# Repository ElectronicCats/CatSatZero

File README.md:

# CaTSatZero

Kit CatSat Zero Education

Manual and more information in our [Wiki](https://github.com/ElectronicCats/CatSatZero/wiki)

Electronic Cats invests time and resources providing this open source design, please support Electronic Cats and open-source hardware by purchasing products from Electronic Cats!

Designed by Electronic Cats.

## License

Firmware released under an GNU AGPL v3.0 license. See the LICENSE file for more information.

Hardware released under an CERN Open Hardware Licence v1.2. See the LICENSE_HARDWARE file for more information.

Electronic Cats is a registered trademark, please do not use if you sell these PCBs.

15 April 2018

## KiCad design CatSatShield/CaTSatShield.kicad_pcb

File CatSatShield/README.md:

# MKR Shield Template

Template of shield family MKR Arduino in KiCad 5

Electronic Cats invests time and resources providing this open source design, please support Electronic Cats and open-source hardware by purchasing products from Electronic Cats!

Designed by Electronic Cats.

Hardware released under an CERN Open Hardware Licence v1.2. See the LICENSE_HARDWARE file for more information.

Electronic Cats is a registered trademark, please do not use if you sell these PCBs.

July 2018

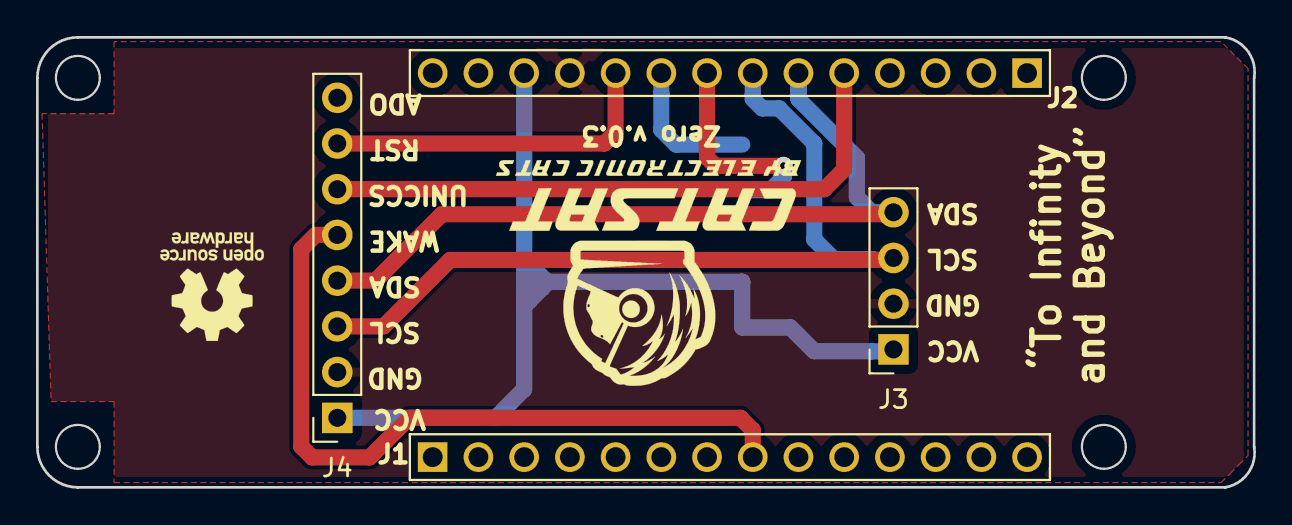
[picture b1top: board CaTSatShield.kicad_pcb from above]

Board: 2 copper layers, 67.6 x 25.0 mm, 14 parts (0 on the bottom side), 9 nets.

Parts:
@HOLE0, @HOLE1, @HOLE2, @HOLE3: (no value)
FRAME1: Page 1; FRAME
J1, J2: 61301411121
J3: BME280; PinSocket_1x04_P2.54mm_Vertical
J4: CCS811; PinSocket_1x08_P2.54mm_Vertical
MODULE1: L80-M39; QUECTEL_L80-M39
U$5, U$6, U$7, U$8: MH_RND_F_2.2MM_NM

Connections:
+3V3: J2.12, J3.1, J4.1, MODULE1.4, MODULE1.5
/10-INTCCS: J2.5, J4.6
/RESET: J2.10, J4.7
/RX: J2.8, MODULE1.2
/SCL: J2.7, J3.3, J4.3
/SDA: J2.6, J3.4, J4.4
/TX: J2.9, MODULE1.1
/WAKEA6: J1.8, J4.5
GND: J2.11, J3.2, J4.2, MODULE1.3, MODULE1.12

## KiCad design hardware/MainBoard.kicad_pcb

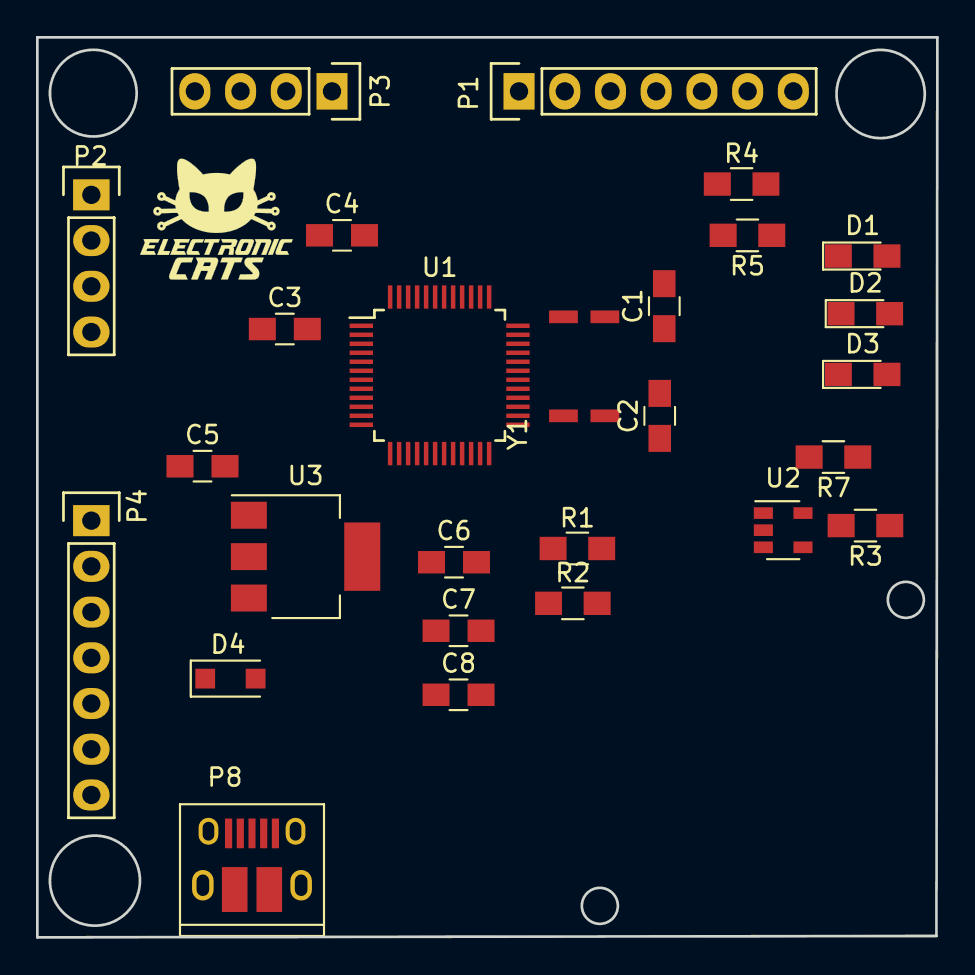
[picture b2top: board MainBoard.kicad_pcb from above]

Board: 2 copper layers, 50.0 x 50.0 mm, 27 parts (0 on the bottom side), 36 nets.

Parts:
C1, C2: 22pF; C_0805_HandSoldering
C3, C4: 1uF; C_0805_HandSoldering
C5, C6: 10uF; C_0805_HandSoldering
C7, C8: 0.1uF; C_0805_HandSoldering
D1, D2, D3: LED; LED_0805_HandSoldering
D4: MBR120; D_SOD-123F
P1, P4: CONN_01X07; Pin_Header_Straight_1x07
P2, P3: CONN_01X04; Pin_Header_Straight_1x04
P8: USB_Micro; USB_Micro-B_10103594-0001LF
R1, R2: 100k; R_0805_HandSoldering
R3: 10k; R_0805_HandSoldering
R4, R5: 1K; R_0805_HandSoldering
R7: 330; R_0805_HandSoldering
U1: ATSAMD21G18A-AU; TQFP-48_7x7mm_Pitch0.5mm
U2: MCP73831T-2ACI/OT; SOT-23-5
U3: AP2114; SOT-223-3_TabPin2
Y1: 32.768; LFXTAL016178Reel

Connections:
+3V3: C6.1, C7.1, C8.1, R4.2, U1.6, U1.17, U1.36, U1.44, U3.2
+BATT: D4.2, P1.2, P4.1, R1.1, U2.3
/A0: P2.4, U1.3
/A1: P2.3, U1.7
/A2: P2.2, U1.8
/A3: P2.1, U1.9
/A4/INT5: P3.2, U1.10
/A5/INT2: P3.1, U1.47
/D5: P3.4, U1.24
/D7: P3.3, U1.30
/D9: R1.2, R2.1, U1.12
/D13: R5.2, U1.26
/D+: P8.3, U1.34
/D-: P8.2, U1.33
/DHT/D6: P1.7, U1.29
/MISO: P4.4, U1.21
/MOSI: P4.5, U1.19
/NSS: P4.6, U1.11
/RFM_RST: P4.7, U1.13
/SCK: P4.3, U1.20
/SCL: P1.3, U1.32
/SDA: P1.4, U1.31
/S_RX: P1.5, U1.38
/S_TX: P1.6, U1.37
GND: C1.1, C2.1, C3.2, C4.2, C5.2, C6.2, C7.2, C8.2, D1.1, D2.1, P1.1, P4.2, P8.5, R2.2, U1.5, U1.18, U1.35, U1.42, U3.1
unnamed: C1.2, U1.2, Y1.1
unnamed: C2.2, U1.1, Y1.2
unnamed: C3.1, U1.4
unnamed: C4.1, U1.43
unnamed: D1.2, R4.1
unnamed: D2.2, R5.1
unnamed: D3.1, R7.1
unnamed: R3.1, U2.5
unnamed: R3.2, U2.2
unnamed: R7.2, U2.1
VCC: C5.1, D3.2, D4.1, U2.4, U3.3

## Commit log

2018-04-15 Schematic Alfa
2018-04-15 Add Licenses
2018-04-17 Add library kicad
2018-04-17 Fix schematic libraries
2018-04-17 check button
2018-04-17 Clean PCB
2018-04-17 Shottcky diode fix
2018-04-27 Assign footprints
2018-05-14 Update netlist
2018-05-14 Update PCB battery Hole
2018-08-01 Update for MakeCode
2018-08-09 Move project to MKR1300 shield
    Change Board base
2018-08-09 Routeo
2018-08-10 Best logos
2018-08-14 Update logos
2018-08-14 Init firmware CatSatZero sensor BMP280 and CCS811
2018-08-14 Add Lora and packet to send
2018-08-21 Fix TX and RX Serial with GPS
2018-08-21 Remove extra layers
2018-08-21 Update version 0.2-beta
    Fix Tx and RX, add logo OSHW
2018-08-21 settings for gerbers
2018-10-02 Fix voltage line
2018-10-02 change connector header x socker J4
2018-10-02 routeo change voltage
2018-10-03 connected pin wakeA6
2018-10-03 Label wakeA6 sch
2018-10-03 Address set ok
2018-10-03 CCS811 working
2018-10-04 Remove duplicate code
2018-10-04 Added voltage battery
2018-10-04 Remove Fº
2018-10-08 Add global variable
2018-10-08 Start LoRa transmition test
2018-10-08 Add first code for groudn station
2018-10-08 Change LoRa communications
2018-10-08 Change payload final format, add function to select channel
2018-10-08 Add function to select channel
2018-10-31 Add led blink for send
2018-10-31 Conversion battery to %
2018-11-01 update to version 0.3
    Update silks
2018-11-01 Change pin names
2018-11-02 Clean LoRa part
2018-11-02 Add Payload descrption
2018-11-05 commentary for CCS811 pin enable
2018-11-05 update blink time delay
2018-11-05 Fix temporal for GPS not data
2018-11-08 add bootloader for MKR1300
2018-11-21 add firmware initial blink
2018-11-22 configure gerbers
2018-12-12 new pins for CatWAN USB Stick
2019-01-17 Update description
2019-01-17 define pins for other boards
2019-01-18 fix typo in serial GPS command
2019-01-18 add optional address
2019-01-18 best format print GPS data
2019-01-24 moved to nmea library
2019-01-25 fix GPS without gps flag
2019-01-26 remove flag gps lost
2019-01-27 add documentation geiger sensor
2019-01-27 define debug
2019-01-27 best comment for pin ccs811
2019-01-27 best comment GPS command
2019-01-28 init version counter geiger
2019-02-03 images
2019-02-03 blink default for catsat zero
2019-02-03 add altitude and velocity GPS
2019-02-03 add radation value in payload
2019-02-03 LED_BUILTIN
2019-02-03 Fix remove extra value
2019-02-03 define raw for geiger
2019-02-03 define raw
2019-02-08 revert library error
2019-02-08 Fix error include library
2019-02-08 enable validation of BME280
2019-02-08 remove F macro
2019-02-08 add debug2 for serial data init
2019-02-08 best detect error in CCS811
2019-02-08 remove data sensor not used
2019-02-09 enable crc
2019-02-09 Debug2 default desactive
2019-02-09 Reduce text
2019-02-09 migrate to adafruit ccs811
2019-02-09 remove temp of ccs811
2019-02-11 track width
2019-02-12 opti blink
2019-02-12 fix typo
2019-02-14 pin name
2019-02-20 assign address in begin
2019-02-20 Check gps received
2019-02-21 update check gps
2019-02-26 Add GPS balloon mode
    Change voltage reference
2019-02-26 Add change to NMEA output
2019-02-26 update to CCS811 adafruit
2019-02-26 Add check wiring GPS
2019-02-27 fix GPS ballon mode
2019-02-27 Mix catsat zero with example geiger
2019-03-01 fix mode ballon
2019-03-02 fix if ballon configured
2019-03-04 Fix balloon mode
2019-03-04 Fiz battery level measurement
2019-03-05 Fix location debug
2019-03-05 Add firmware version
2019-03-05 Add interrupt service for data received
2019-04-05 change lora library
2019-05-22 update gitgnore
2019-05-22 add logo catsat zero!
2019-07-26 Test write function instead of print
2019-11-04 Update DEBUG comments
